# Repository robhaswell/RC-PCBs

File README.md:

# RC-PCBs
Various PCBs to help with my RC projects.

## <a href="Halogen discharger">Halogen discharger</a>
A 300W or 600W discharging circuit using 50W GY6.35 halogen bulbs.

# Top hats
A "top hat" is a name given to a PCB designed to provide an interface between RC helicopter avionics (servos, BEC etc) and common drone flight controllers.
The main goal is to provide a stable plug for servos, but also help in any other way they can.

## <a href="Top hats/16mm Blade">16mm for Blade 150 S / 180 CFX</a>
This PCB was designed for for a TeenyF4. The pad order matches the 6-way multicable shipped with the FC. Cut the cable in half, strip all the ends, and solder them in order to the pads.
You will also need to solder another lead from the LED_STRIP pad onto pad 7 to provide the additional control wire for the main motor.
One of your ESCs should have a BEC providing +5V to one of the 3-pin headers.
A spare pair of pads is provided to access this power rail, for e.g. RX or Blackbox.

# Instructions for ordering

You can order any PCB with a prototyping service.
Below are instructions for using [JLCPCB](https://jlcpcb.com):

1. Visit https://jlcpcb.com/.
2. Click "Order now' from the menu - do not use the quoting box.
3. Upload the file [gerber.zip](gerber.zip).
4. You may use the default options, but I suggest selecting a thickness of 0.8mm or 1.0mm. I also prefer the black PCBs.
5. Add to basket and check out. Take care to review the shipping options. FedEx is good if you would like this sooner, but Special Air Line is usually a very cheap option depending on your location.

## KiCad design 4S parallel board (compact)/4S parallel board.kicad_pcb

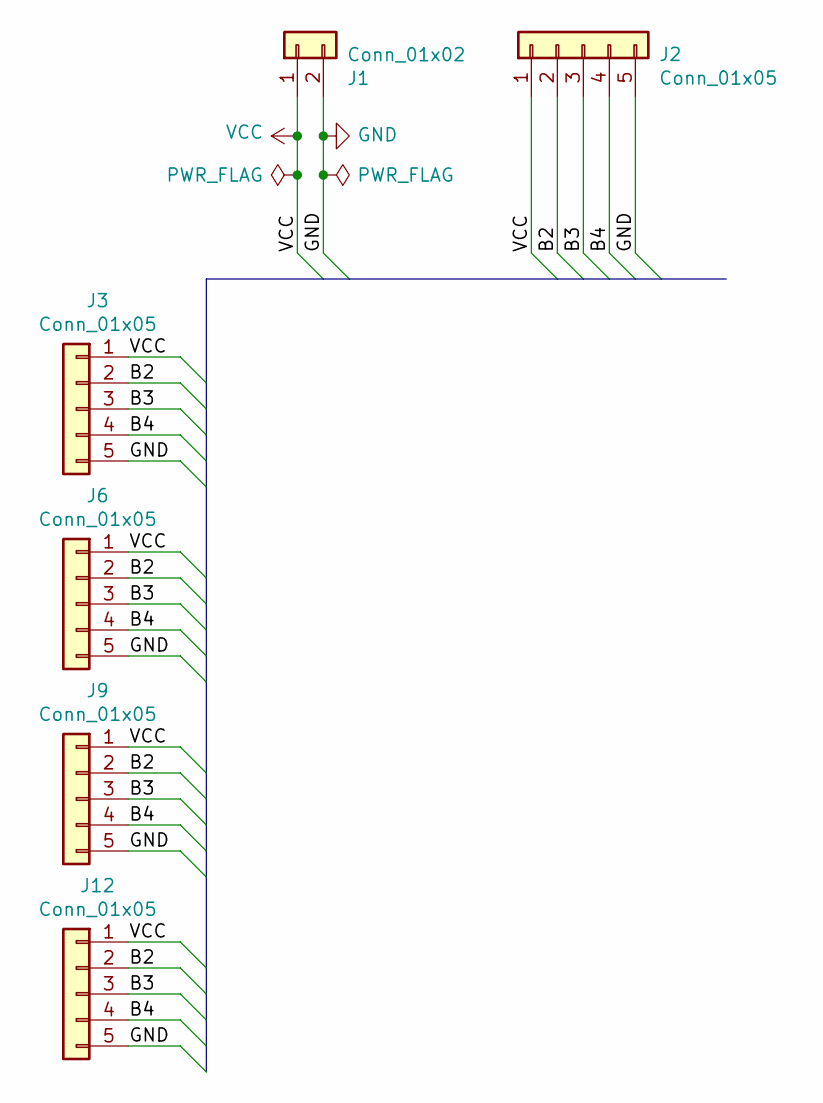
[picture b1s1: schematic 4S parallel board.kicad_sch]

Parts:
J1: Conn_01x02; SolderWire-1.5sqmm_1x02_P6mm_D1.7mm_OD3mm
J2, J3, J9, J12: Conn_01x05; JST_XH_B5B-XH-A_1x05_P2.50mm_Vertical
J6: Conn_01x05; PinHeader_1x05_P2.54mm_Vertical

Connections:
/B2: J2.2, J3.2, J6.2, J9.2, J12.2
/B3: J2.3, J3.3, J6.3, J9.3, J12.3
/B4: J2.4, J3.4, J6.4, J9.4, J12.4
GND: J1.2, J2.5, J3.5, J6.5, J9.5, J12.5
VCC: J1.1, J2.1, J3.1, J6.1, J9.1, J12.1

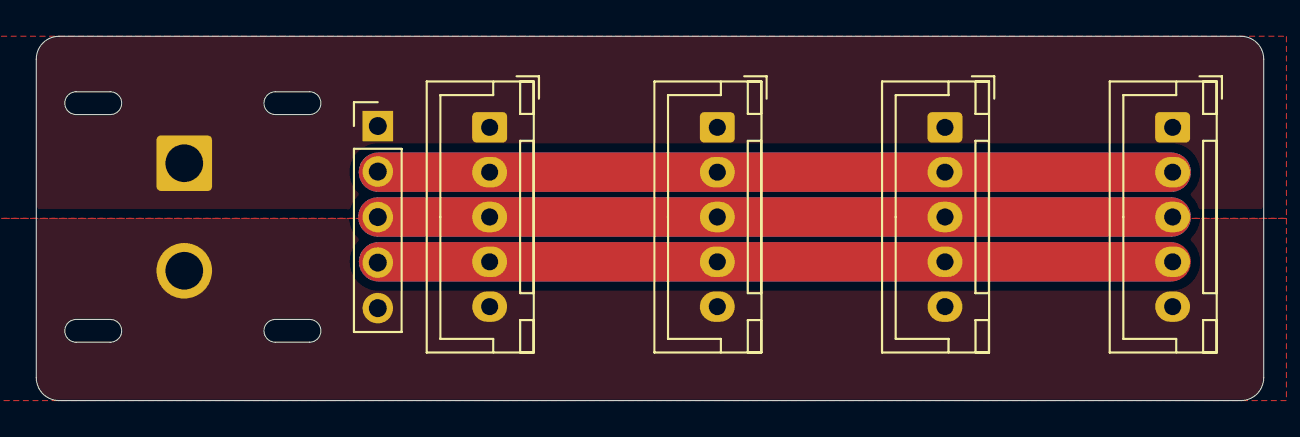
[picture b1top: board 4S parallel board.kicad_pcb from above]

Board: 2 copper layers, 68.5 x 20.3 mm, 6 parts (0 on the bottom side), 5 nets.

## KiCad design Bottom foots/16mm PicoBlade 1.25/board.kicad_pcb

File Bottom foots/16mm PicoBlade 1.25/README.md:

# 16mm FC, JST-ZH 1.5mm connectors, Happymodel EP RX

Suggested uses: 16mm flight controller in a Blade 150 S or 180 CFX. Includes headers for a floating Happymodel EP1 or EP2.

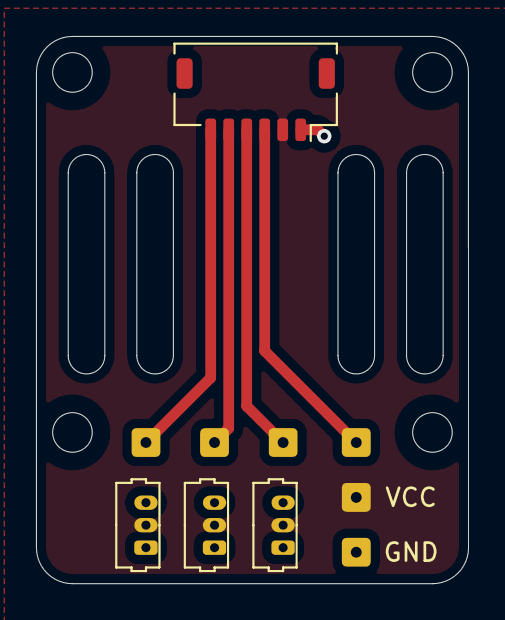
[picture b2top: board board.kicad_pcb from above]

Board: 2 copper layers, 24.0 x 30.4 mm, 14 parts (0 on the bottom side), 6 nets.

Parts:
H1, H2, H3, H4: MountingHole; MountingHole_2.2mm_M2
J1: Conn_01x06; JST_SHL_SM06B-SHLS-TF_1x06-1MP_P1.00mm_Horizontal
J2, J3, J4: Conn_01x03; Molex_PicoBlade_53047-0310_1x03_P1.25mm_Vertical
J6, J7, J8, J9, J10, J13: Conn_01x01; SolderWire-0.1sqmm_1x01_D0.4mm_OD1mm

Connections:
+BATT: J1.2, J2.2, J3.2, J4.2, J10.1
GND: J1.1, J2.1, J3.1, J4.1, J6.1
unnamed: J1.3, J9.1
unnamed: J1.4, J4.3, J8.1
unnamed: J1.5, J3.3, J7.1
unnamed: J1.6, J2.3, J13.1

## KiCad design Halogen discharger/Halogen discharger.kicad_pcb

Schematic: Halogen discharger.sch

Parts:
H1, H2, H3, H4: MountingHole; MountingHole_2.2mm_M2
J1: Conn_01x02; AMASS_XT30PW-F_1x02_P2.50mm_Horizontal
J2, J3, J4, J5: Conn_01x01; SolderWirePad_1x01_SMD_1x2mm
LA1, LA2, LA3, LA4, LA5, LA6, LA7, LA8, LA9, LA10, LA11, LA12: Lamp; GY6.35

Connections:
GND: J1.1, J3.1, J5.1, LA4.1 (-), LA8.1 (-), LA12.1 (-)
unnamed: LA1.1 (-), LA2.2 (+), LA5.1 (-), LA6.2 (+), LA9.1 (-), LA10.2 (+)
unnamed: LA2.1 (-), LA3.2 (+), LA6.1 (-), LA7.2 (+), LA10.1 (-), LA11.2 (+)
unnamed: LA3.1 (-), LA4.2 (+), LA7.1 (-), LA8.2 (+), LA11.1 (-), LA12.2 (+)
VCC: J1.2, J2.1, J4.1, LA1.2 (+), LA5.2 (+), LA9.2 (+)

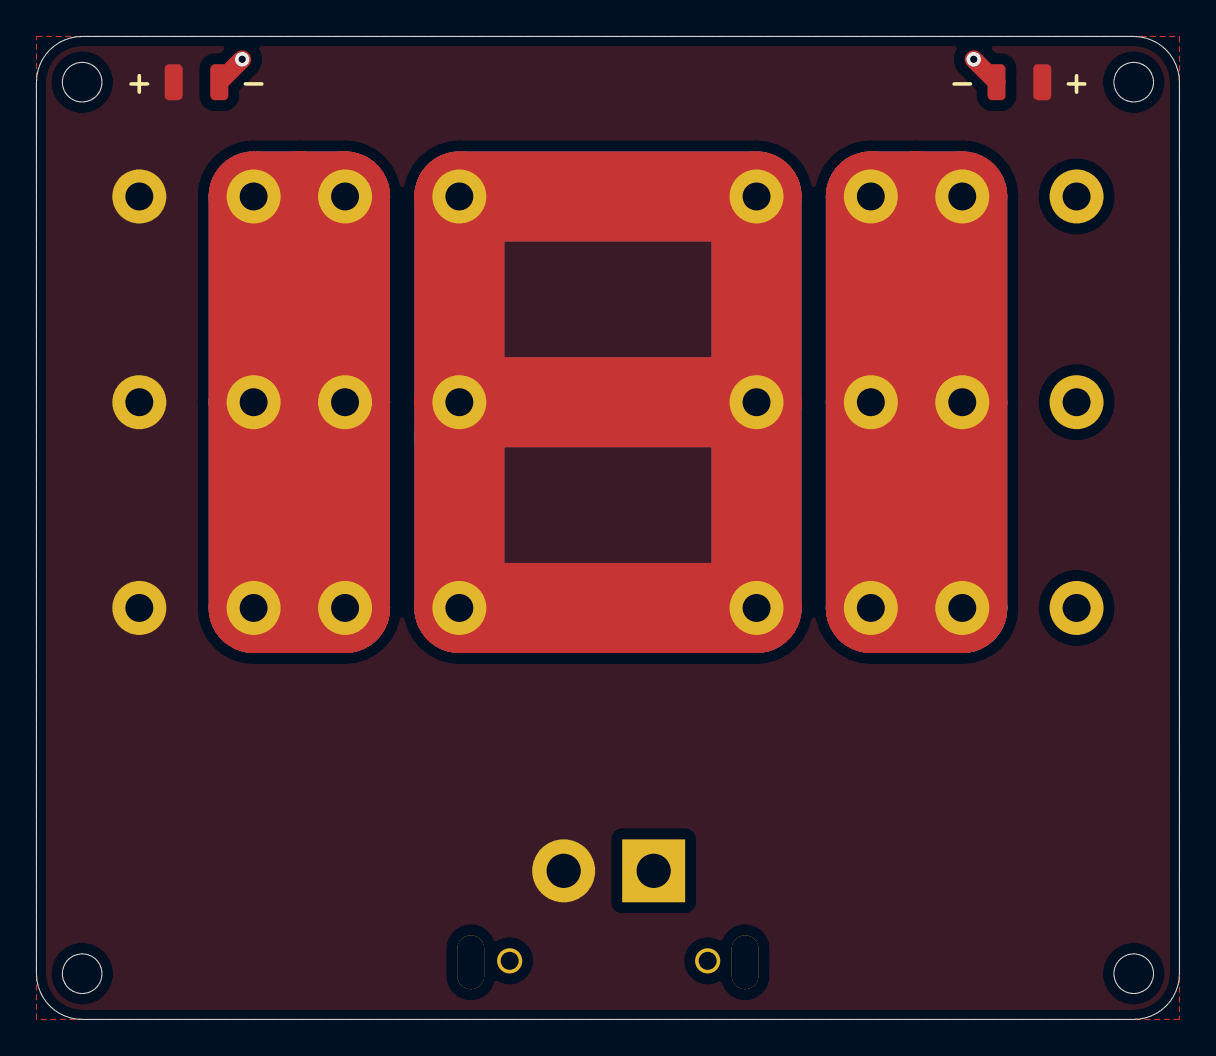
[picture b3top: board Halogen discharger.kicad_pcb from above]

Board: 2 copper layers, 63.5 x 54.6 mm, 21 parts (0 on the bottom side), 5 nets.

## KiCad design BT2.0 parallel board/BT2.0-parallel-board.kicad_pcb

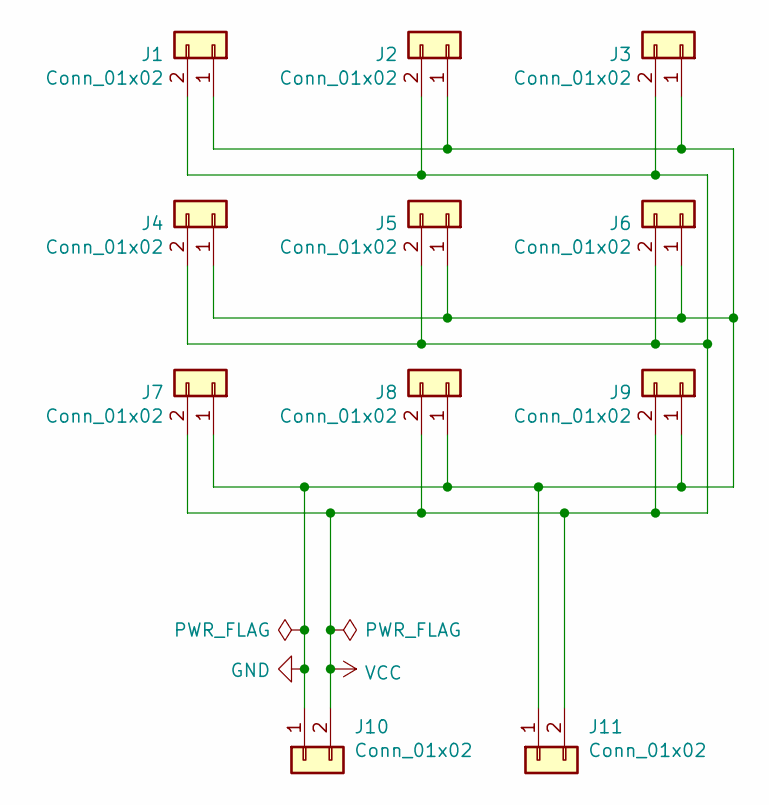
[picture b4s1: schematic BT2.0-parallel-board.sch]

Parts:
J1, J2, J3, J4, J5, J6, J7, J8, J9: Conn_01x02; BT2.0-M
J10, J11: Conn_01x02; AMASS_XT30PW-F_1x02_P2.50mm_Horizontal

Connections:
GND: J1.1, J2.1, J3.1, J4.1, J5.1, J6.1, J7.1, J8.1, J9.1, J10.1, J11.1
VCC: J1.2, J2.2, J3.2, J4.2, J5.2, J6.2, J7.2, J8.2, J9.2, J10.2, J11.2

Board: 2 copper layers, 11 parts (0 on the bottom side), 2 nets, no tracks yet.

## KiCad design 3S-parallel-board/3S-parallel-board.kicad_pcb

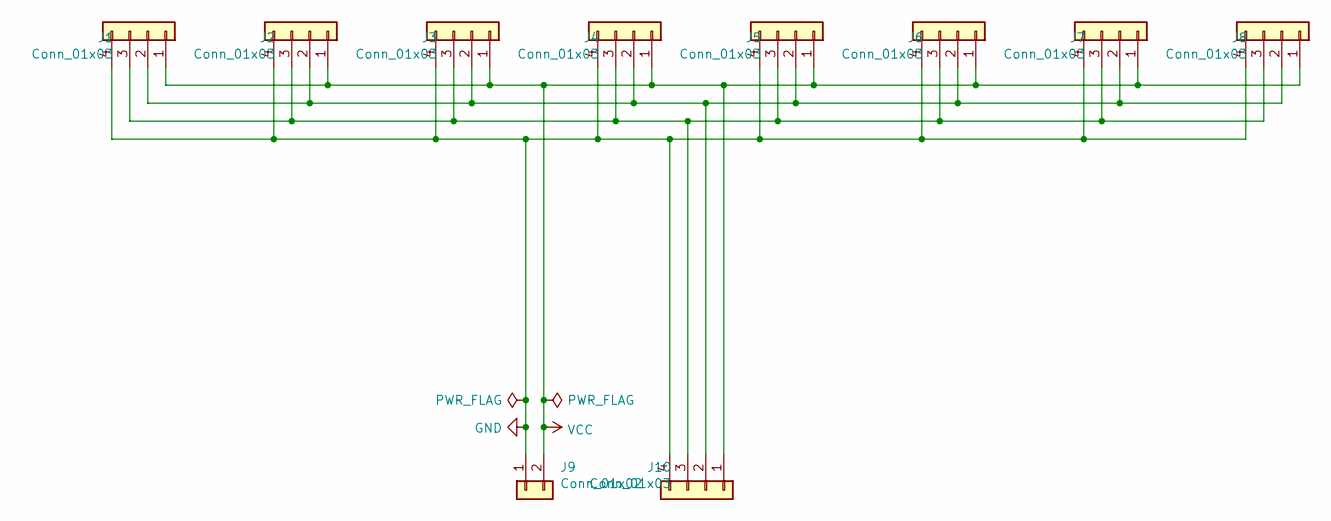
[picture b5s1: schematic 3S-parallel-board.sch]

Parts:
J1, J2, J3, J4, J5, J6, J7, J8: Conn_01x03; JST_XH_B4B-XH-A_1x04_P2.50mm_Vertical
J9: Conn_01x02; AMASS_XT30PW-F_1x02_P2.50mm_Horizontal
J10: Conn_01x03; JST_XH_S4B-XH-A_1x04_P2.50mm_Horizontal

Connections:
GND: J1.4, J2.4, J3.4, J4.4, J5.4, J6.4, J7.4, J8.4, J9.1, J10.4
unnamed: J1.2, J2.2, J3.2, J4.2, J5.2, J6.2, J7.2, J8.2, J10.2
unnamed: J1.3, J2.3, J3.3, J4.3, J5.3, J6.3, J7.3, J8.3, J10.3
VCC: J1.1, J2.1, J3.1, J4.1, J5.1, J6.1, J7.1, J8.1, J9.2, J10.1

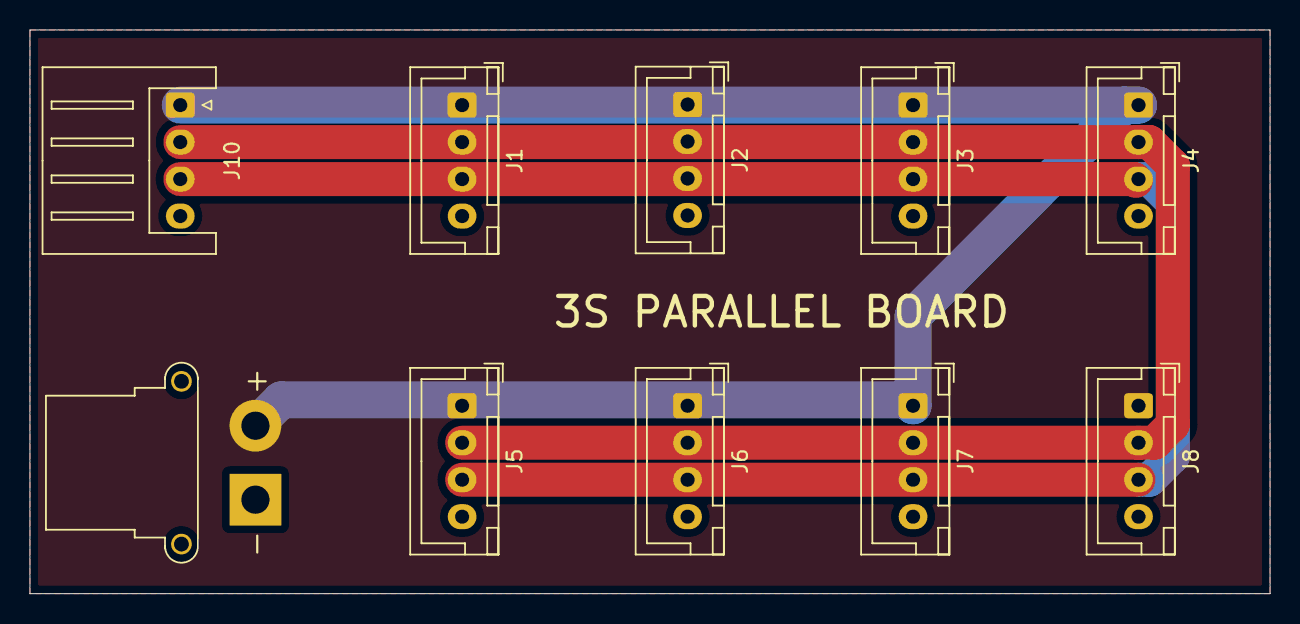
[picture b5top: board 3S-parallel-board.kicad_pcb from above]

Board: 2 copper layers, 83.8 x 38.1 mm, 10 parts (0 on the bottom side), 4 nets.

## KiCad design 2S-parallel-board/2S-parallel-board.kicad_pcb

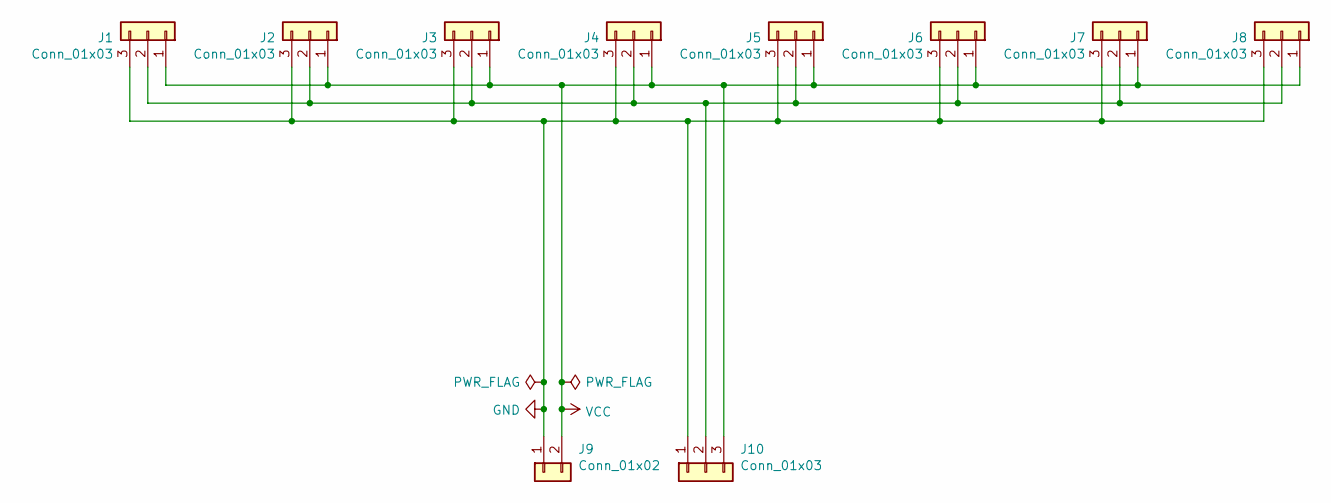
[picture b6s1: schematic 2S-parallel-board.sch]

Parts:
J1, J2, J3, J4, J5, J6, J7, J8: Conn_01x03; JST_XH_B3B-XH-A_1x03_P2.50mm_Vertical
J9: Conn_01x02; AMASS_XT30PW-F_1x02_P2.50mm_Horizontal
J10: Conn_01x03; JST_XH_S3B-XH-A_1x03_P2.50mm_Horizontal

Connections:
GND: J1.3, J2.3, J3.3, J4.3, J5.3, J6.3, J7.3, J8.3, J9.1, J10.1
unnamed: J1.2, J2.2, J3.2, J4.2, J5.2, J6.2, J7.2, J8.2, J10.2
VCC: J1.1, J2.1, J3.1, J4.1, J5.1, J6.1, J7.1, J8.1, J9.2, J10.3

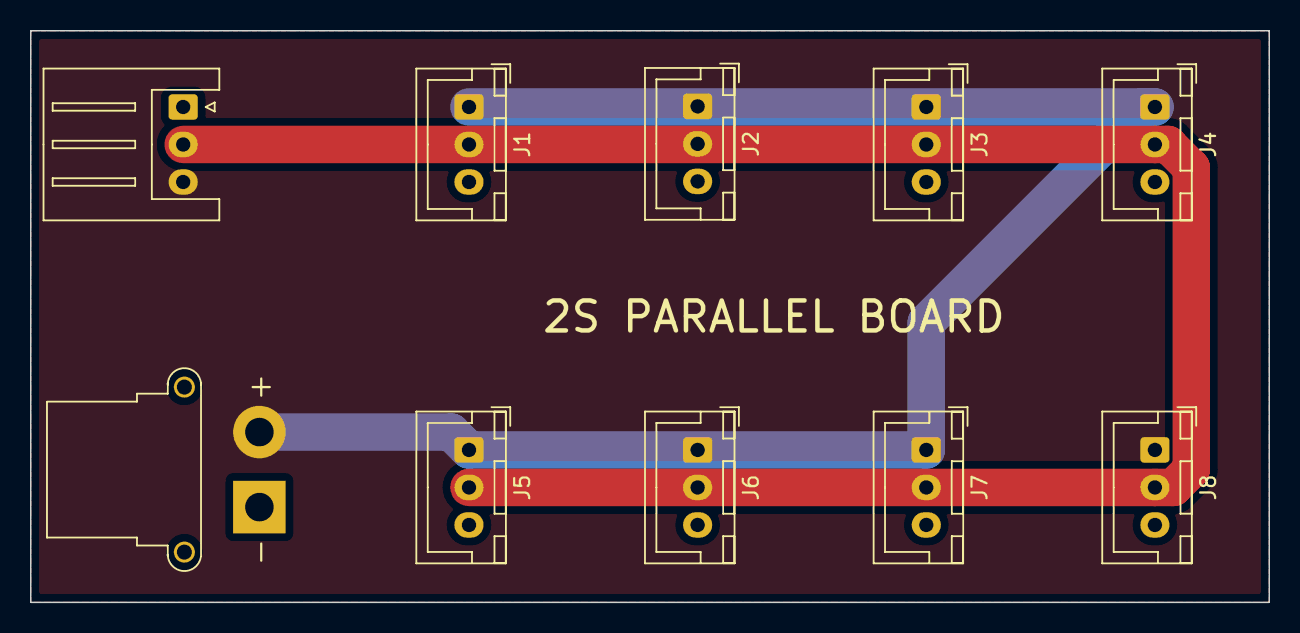
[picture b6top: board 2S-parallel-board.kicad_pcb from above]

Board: 2 copper layers, 82.5 x 38.1 mm, 10 parts (0 on the bottom side), 3 nets.

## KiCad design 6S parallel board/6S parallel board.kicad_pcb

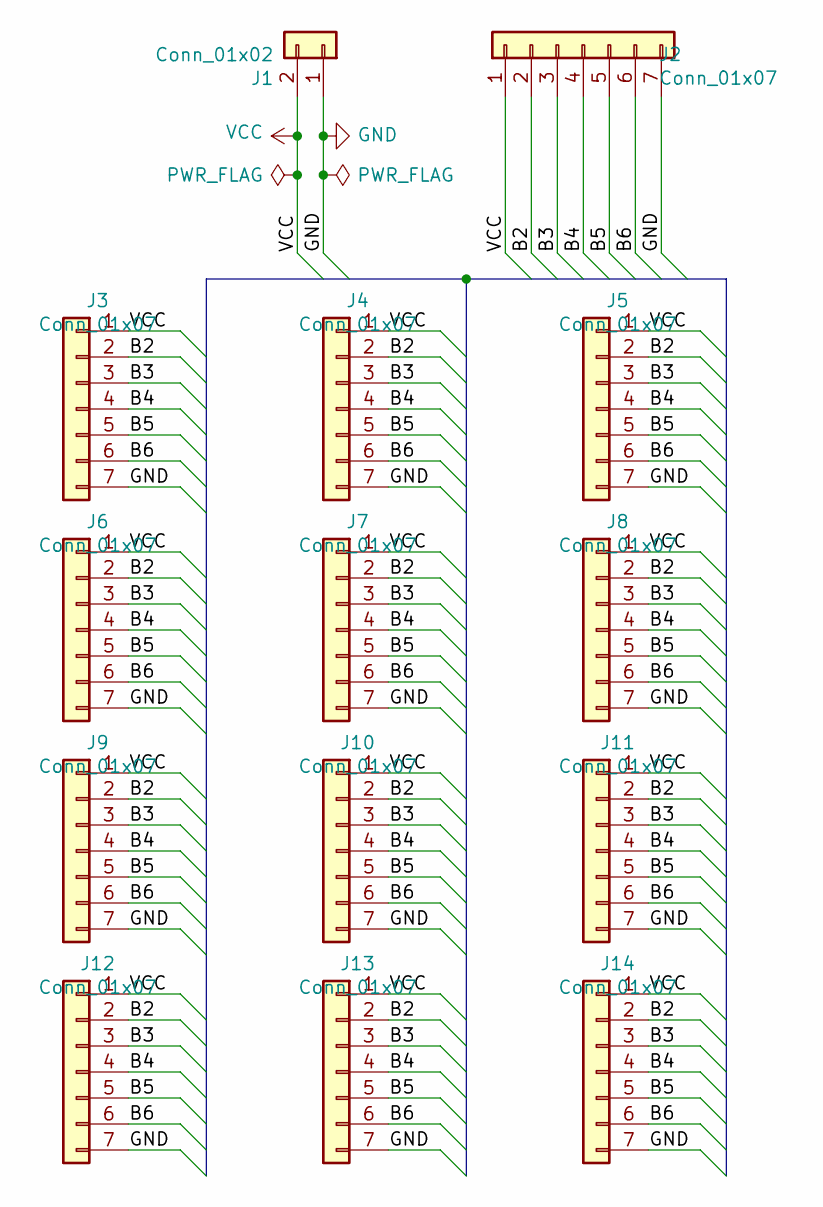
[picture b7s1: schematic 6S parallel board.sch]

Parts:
J1: Conn_01x02; AMASS_XT30PW-F_1x02_P2.50mm_Horizontal
J2: Conn_01x07; JST_XH_S7B-XH-A_1x07_P2.50mm_Horizontal
J3, J4, J5, J6, J7, J8, J9, J10, J11, J12, J13, J14: Conn_01x07; JST_XH_B7B-XH-A_1x07_P2.50mm_Vertical

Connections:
/B2: J2.2, J3.2, J4.2, J5.2, J6.2, J7.2, J8.2, J9.2, J10.2, J11.2, J12.2, J13.2, J14.2
/B3: J2.3, J3.3, J4.3, J5.3, J6.3, J7.3, J8.3, J9.3, J10.3, J11.3, J12.3, J13.3, J14.3
/B4: J2.4, J3.4, J4.4, J5.4, J6.4, J7.4, J8.4, J9.4, J10.4, J11.4, J12.4, J13.4, J14.4
/B5: J2.5, J3.5, J4.5, J5.5, J6.5, J7.5, J8.5, J9.5, J10.5, J11.5, J12.5, J13.5, J14.5
/B6: J2.6, J3.6, J4.6, J5.6, J6.6, J7.6, J8.6, J9.6, J10.6, J11.6, J12.6, J13.6, J14.6
GND: J1.1, J2.7, J3.7, J4.7, J5.7, J6.7, J7.7, J8.7, J9.7, J10.7, J11.7, J12.7, J13.7, J14.7
VCC: J1.2, J2.1, J3.1, J4.1, J5.1, J6.1, J7.1, J8.1, J9.1, J10.1, J11.1, J12.1, J13.1, J14.1

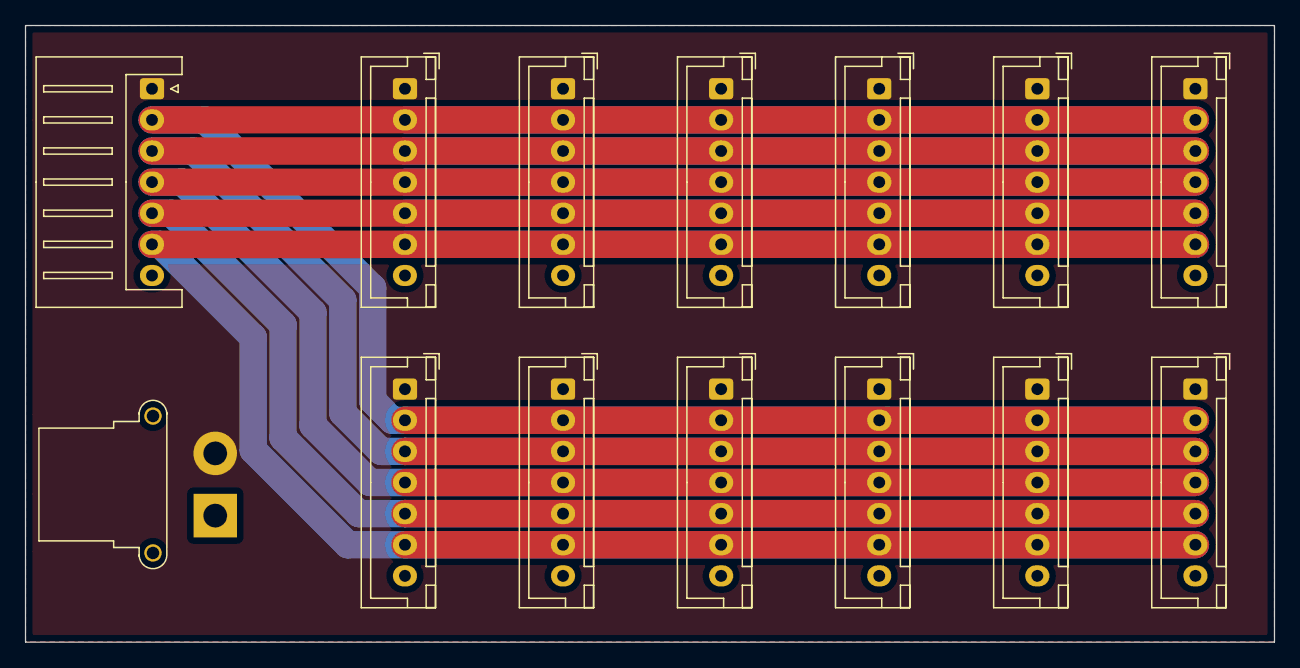
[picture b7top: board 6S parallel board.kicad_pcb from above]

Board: 2 copper layers, 100.3 x 49.5 mm, 14 parts (0 on the bottom side), 7 nets.

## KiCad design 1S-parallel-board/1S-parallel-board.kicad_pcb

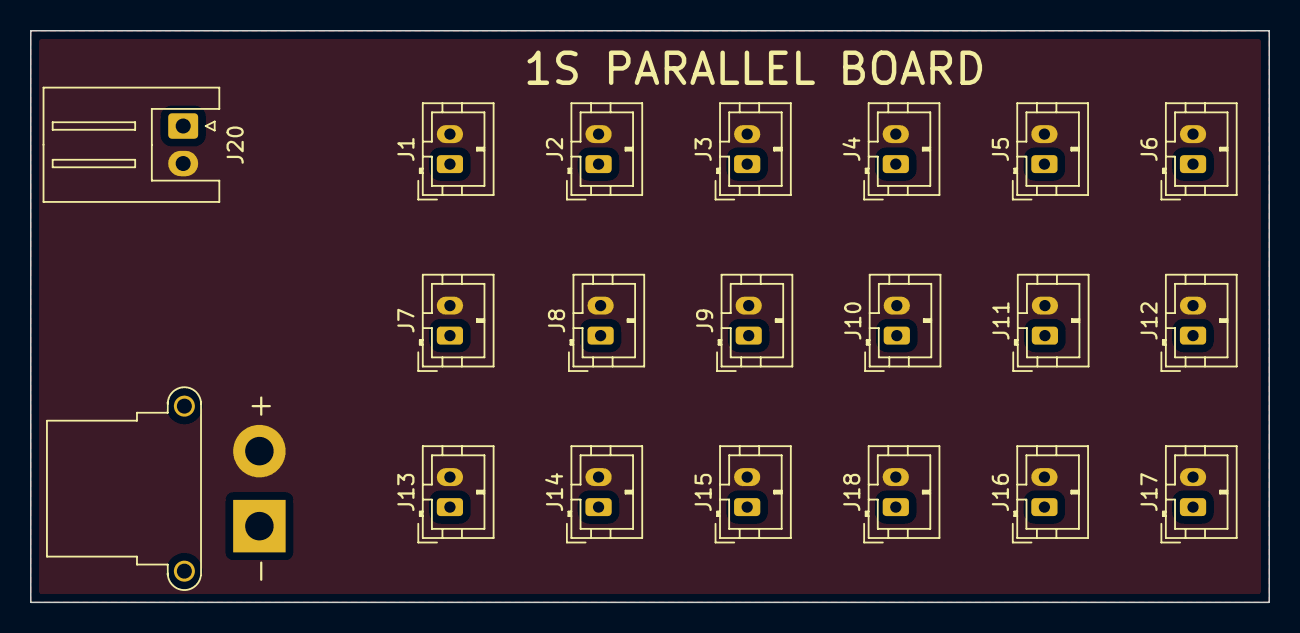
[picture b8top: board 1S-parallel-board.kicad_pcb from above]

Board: 2 copper layers, 82.5 x 38.1 mm, 20 parts (0 on the bottom side), 2 nets, no tracks yet.

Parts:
J1, J2, J3, J4, J5, J6, J7, J8, J9, J10, J11, J12, J13, J14, J15, J16, J17, J18: Conn_01x02; JST_PH_B2B-PH-K_1x02_P2.00mm_Vertical
J19: Conn_01x02; AMASS_XT30PW-F_1x02_P2.50mm_Horizontal
J20: Conn_01x02; JST_XH_S2B-XH-A_1x02_P2.50mm_Horizontal

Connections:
GND: J1.1, J2.1, J3.1, J4.1, J5.1, J6.1, J7.1, J8.1, J9.1, J10.1, J11.1, J12.1, J13.1, J14.1, J15.1, J16.1, J17.1, J18.1, J19.1, J20.1
VCC: J1.2, J2.2, J3.2, J4.2, J5.2, J6.2, J7.2, J8.2, J9.2, J10.2, J11.2, J12.2, J13.2, J14.2, J15.2, J16.2, J17.2, J18.2, J19.2, J20.2

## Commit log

2021-11-05 Halogen discharger and top hat for 150 S
2021-11-05 Add some readmes and layout.
2022-05-15 Loads of boards.
2022-05-30 First bottom foot
2022-05-30 Halogen discharger updates.
2022-05-30 Happymodel EP version.
2022-05-30 README for first PCB
2022-05-30 Space out the VCC path a bit.
2022-05-30 Less path for voltage than I would like but the current values here aren't large
2022-05-30 Blade 150 S board
2022-05-30 Update Gerber file names
2022-05-30 1.25mm PCB
2022-05-30 Rename 1.5 board - has no EP
2023-05-02 Bottom foots.
2023-05-02 Compact 4S parallel board
